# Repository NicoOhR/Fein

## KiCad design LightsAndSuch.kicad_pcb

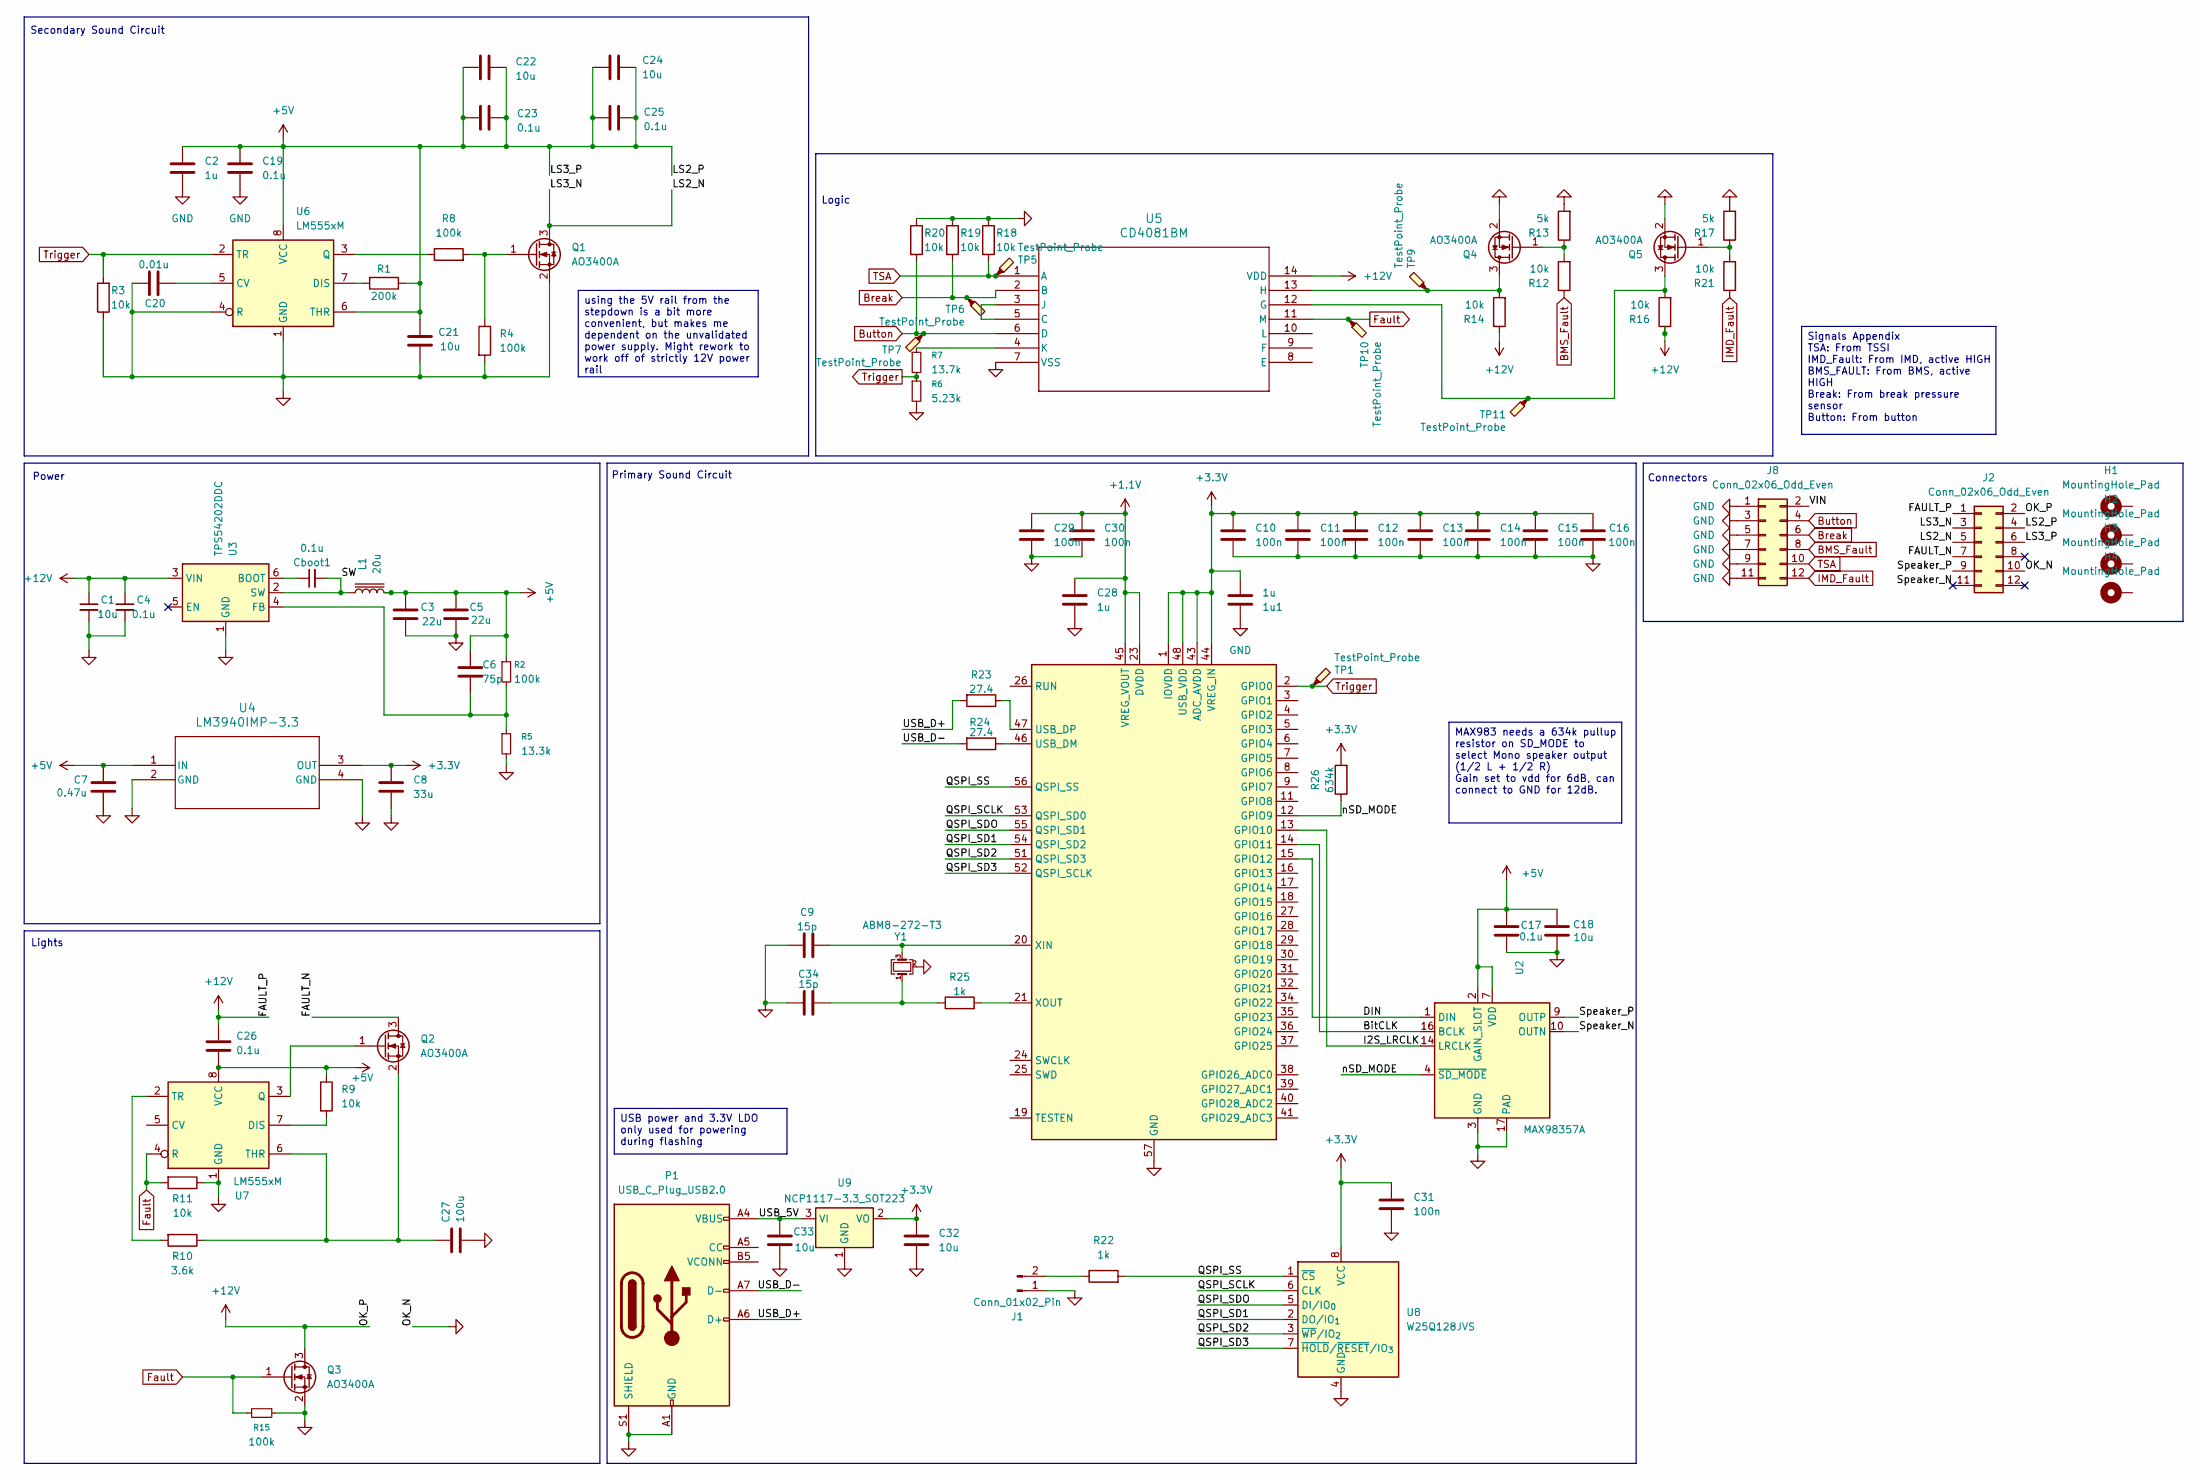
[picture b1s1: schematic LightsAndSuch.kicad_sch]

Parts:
1u1: 1u; C_0603_1608Metric_Pad1.08x0.95mm_HandSolder
C1, C18, C21, C22, C24, C32, C33: 10u; C_0603_1608Metric_Pad1.08x0.95mm_HandSolder
C2, C28: 1u; C_0603_1608Metric_Pad1.08x0.95mm_HandSolder
C3, C5: 22u; C_0603_1608Metric_Pad1.08x0.95mm_HandSolder
C4, C17, C19, C23, C25, C26: 0.1u; C_0603_1608Metric_Pad1.08x0.95mm_HandSolder
C6: 75p; C_0603_1608Metric_Pad1.08x0.95mm_HandSolder
C7: 0.47u; C_0603_1608Metric_Pad1.08x0.95mm_HandSolder
C8: 33u; C_0603_1608Metric_Pad1.08x0.95mm_HandSolder
C9, C34: 15p; C_0603_1608Metric_Pad1.08x0.95mm_HandSolder
C10, C11, C12, C13, C14, C15, C16, C29, C30, C31: 100n; C_0603_1608Metric_Pad1.08x0.95mm_HandSolder
C20: 0.01u; C_0603_1608Metric_Pad1.08x0.95mm_HandSolder
C27: 100u; C_0603_1608Metric_Pad1.08x0.95mm_HandSolder
Cboot1: 0.1u; C_0603_1608Metric_Pad1.08x0.95mm_HandSolder
H1, H2, H3, H4: MountingHole_Pad; MountingHole_4.3mm_M4_DIN965_Pad
J1: Conn_01x02_Pin; PinHeader_1x02_P2.00mm_Vertical
J2, J8: Conn_02x06_Odd_Even; Hirose_DF11-12DP-2DSA_2x06_P2.00mm_Vertical
L1: 20u; L_0603_1608Metric
P1: USB_C_Plug_USB2.0; USB_C_Receptacle_Amphenol_124019772112A
Q1, Q2, Q3, Q4, Q5: AO3400A; SOT-23
R1: 200k; R_0603_1608Metric_Pad0.98x0.95mm_HandSolder
R2, R4, R8, R15: 100k; R_0603_1608Metric_Pad0.98x0.95mm_HandSolder
R3, R9, R11, R12, R14, R16, R18, R19, R20, R21: 10k; R_0603_1608Metric_Pad0.98x0.95mm_HandSolder
R5: 13.3k; R_0603_1608Metric_Pad0.98x0.95mm_HandSolder
R6: 5.23k; R_0603_1608Metric_Pad0.98x0.95mm_HandSolder
R7: 13.7k; R_0603_1608Metric_Pad0.98x0.95mm_HandSolder
R10: 3.6k; R_0603_1608Metric_Pad0.98x0.95mm_HandSolder
R13, R17: 5k; R_0603_1608Metric_Pad0.98x0.95mm_HandSolder
R22, R25: 1k; R_0603_1608Metric_Pad0.98x0.95mm_HandSolder
R23, R24: 27.4; R_0603_1608Metric_Pad0.98x0.95mm_HandSolder
R26: 634k; R_0603_1608Metric_Pad0.98x0.95mm_HandSolder
TP1, TP5, TP6, TP7, TP9, TP10, TP11: TestPoint_Probe; HARWIN_S2761-46R
U1: RP2040; QFN-56-1EP_7x7mm_P0.4mm_EP3.2x3.2mm
U2: MAX98357A; TQFN-16-1EP_3x3mm_P0.5mm_EP1.23x1.23mm
U3: TPS54202DDC; SOT-23-6
U4: LM3940IMP-3.3; MP04A
U5: CD4081BM; DIP-14_W7.62mm
U6, U7: LM555xM; SOIC-8_3.9x4.9mm_P1.27mm
U8: W25Q128JVS; SOIC-8_5.3x5.3mm_P1.27mm
U9: NCP1117-3.3_SOT223; SOT-223-3_TabPin2
Y1: ABM8-272-T3; Crystal_SMD_3225-4Pin_3.2x2.5mm_HandSoldering

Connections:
+1.1V: C28.1, C29.1, C30.1, U1.23 (DVDD), U1.45 (VREG_VOUT), U1.50 (DVDD)
+3.3V: 1u1.2, C8.1, C10.1, C11.1, C12.1, C13.1, C14.1, C15.1, C16.1, C31.1, C32.1, R26.2, U1.1 (IOVDD), U1.10 (IOVDD), U1.22 (IOVDD), U1.33 (IOVDD), U1.42 (IOVDD), U1.43 (ADC_AVDD), U1.44 (VREG_IN), U1.48 (USB_VDD), U1.49 (IOVDD), U4.3 (OUT), U8.8 (VCC), U9.2 (VO)
+5V: C2.1, C3.1, C5.1, C6.1, C7.1, C17.2, C18.2, C19.1, C21.2, C22.1, C22.2, C23.1, C23.2, C24.1, C24.2, C25.1, C25.2, C26.1, J2.4, J2.6, L1.2, R1.1, R2.1, R9.1, U2.2 (GAIN_SLOT), U2.7 (VDD), U2.8 (VDD), U4.1 (IN), U6.6 (THR), U6.8 (VCC), U7.8 (VCC)
+12V: C1.1, C4.1, C26.2, J2.1, J2.2, Q3.3 (D), R14.1, R16.1, U3.3 (VIN), U5.14 (VDD)
/BitCLK: U1.14 (GPIO11), U2.16 (BCLK)
/DIN: U1.15 (GPIO12), U2.1 (DIN)
/FAULT_N: J2.7, Q2.3 (D)
/I2S_LRCLK: U1.13 (GPIO10), U2.14 (LRCLK)
/LS2_N: J2.3, J2.5, Q1.3 (D)
/QSPI_SCLK: U1.53 (QSPI_SD0), U8.6 (CLK)
/QSPI_SD1: U1.54 (QSPI_SD2), U8.2 (DO/IO_{1})
/QSPI_SD2: U1.51 (QSPI_SD3), U8.3 (~WP/IO_{2})
/QSPI_SD3: U1.52 (QSPI_SCLK), U8.7 (~HOLD/~RESET/IO_{3})
/QSPI_SDO: U1.55 (QSPI_SD1), U8.5 (DI/IO_{0})
/QSPI_SS: R22.2, U1.56 (QSPI_SS), U8.1 (~CS)
/SW: Cboot1.2, L1.1, U3.2 (SW)
/Speaker_N: J2.11, U2.10 (OUTN)
/Speaker_P: J2.9, U2.9 (OUTP)
/USB_5V: C33.1, P1.A4 (VBUS), P1.A9 (VBUS), P1.B4 (VBUS), P1.B9 (VBUS), U9.3 (VI)
/USB_D+: P1.A6 (D+), R23.2
/USB_D-: P1.A7 (D-), R24.2
/VIN: J8.2
/nSD_MODE: R26.1, U1.12 (GPIO9), U2.4 (~SD_MODE)
BMS_Fault: J8.8, R12.1
Break: J8.6, R19.2, TP6.1, U5.2 (B)
Button: J8.4, R20.2, TP7.1, U5.6 (D)
Fault: Q3.1 (G), R11.2, R15.2, TP10.1, U5.11 (M), U7.4 (R)
GND: 1u1.1, C1.2, C2.2, C3.2, C4.2, C5.2, C7.2, C8.2, C9.1, C10.2, C11.2, C12.2, C13.2, C14.2, C15.2, C16.2, C17.1, C18.1, C19.2, C20.2, C21.1, C27.1, C28.2, C29.2, C30.2, C31.2, C32.2, C33.2, C34.1, J1.1, J2.10, J8.1, J8.3, J8.5, J8.7, J8.9, J8.11, P1.A1 (GND), P1.A12 (GND), P1.B1 (GND), P1.B12 (GND), P1.S1 (SHIELD), Q1.2 (S), Q3.2 (S), Q4.2 (S), Q5.2 (S), R3.1, R4.2, R5.2, R6.2, R11.1, R13.2, R15.1, R17.2, R18.1, R19.1, R20.1, U1.57 (GND), U2.3 (GND), U2.11 (GND), U2.15 (GND), U2.17 (PAD), U3.1 (GND), U4.2 (GND), U4.4 (GND), U5.7 (VSS), U6.1 (GND), U6.4 (R), U7.1 (GND), U8.4 (GND), U9.1 (GND), Y1.2 (G), Y1.4 (G)
IMD_Fault: J8.12, R21.1
unnamed: C34.2, R25.1, Y1.1
unnamed: J1.2, R22.1
unnamed: Q1.1 (G), R4.1, R8.2
unnamed: Q2.1 (G), U7.3 (Q)
unnamed: C27.2, Q2.2 (S), R10.1, U7.6 (THR)
unnamed: Q4.3 (D), R14.2, TP9.1, U5.13 (H)
unnamed: Q4.1 (G), R12.2, R13.1
unnamed: Q5.3 (D), R16.2, TP11.1, U5.12 (G)
unnamed: Q5.1 (G), R17.1, R21.2
unnamed: R24.1, U1.46 (USB_DM)
unnamed: R23.1, U1.47 (USB_DP)
unnamed: C9.2, U1.20 (XIN), Y1.3
unnamed: R25.2, U1.21 (XOUT)
unnamed: Cboot1.1, U3.6 (BOOT)
unnamed: C6.2, R2.2, R5.1, U3.4 (FB)
unnamed: U5.3 (J), U5.5 (C)
unnamed: R7.1, U5.4 (K)
unnamed: C20.1, U6.5 (CV)
unnamed: R1.2, U6.7 (DIS)
unnamed: R8.1, U6.3 (Q)
unnamed: R9.2, U7.7 (DIS)
unnamed: R10.2, U7.2 (TR)
TSA: J8.10, R18.2, TP5.1, U5.1 (A)
Trigger: R3.2, R6.1, R7.2, TP1.1 (1_1), U1.2 (GPIO0), U6.2 (TR)

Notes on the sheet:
Logic
Lights
Secondary Sound Circuit
Connectors
Power
Primary Sound Circuit
Signals Appendix TSA: From TSSI IMD_Fault: From IMD, active HIGH BMS_FAULT: From BMS, active HIGH Break: From break pressure sensor Button: From button
USB power and 3.3V LDO only used for powering during flashing
using the 5V rail from the stepdown is a bit more convenient, but makes me dependent on the unvalidated power supply. Might rework to work off of strictly 12V power rail
MAX983 needs a 634k pullup resistor on SD_MODE to select Mono speaker output (1/2 L + 1/2 R) Gain set to vdd for 6dB, can connect to GND for 12dB.

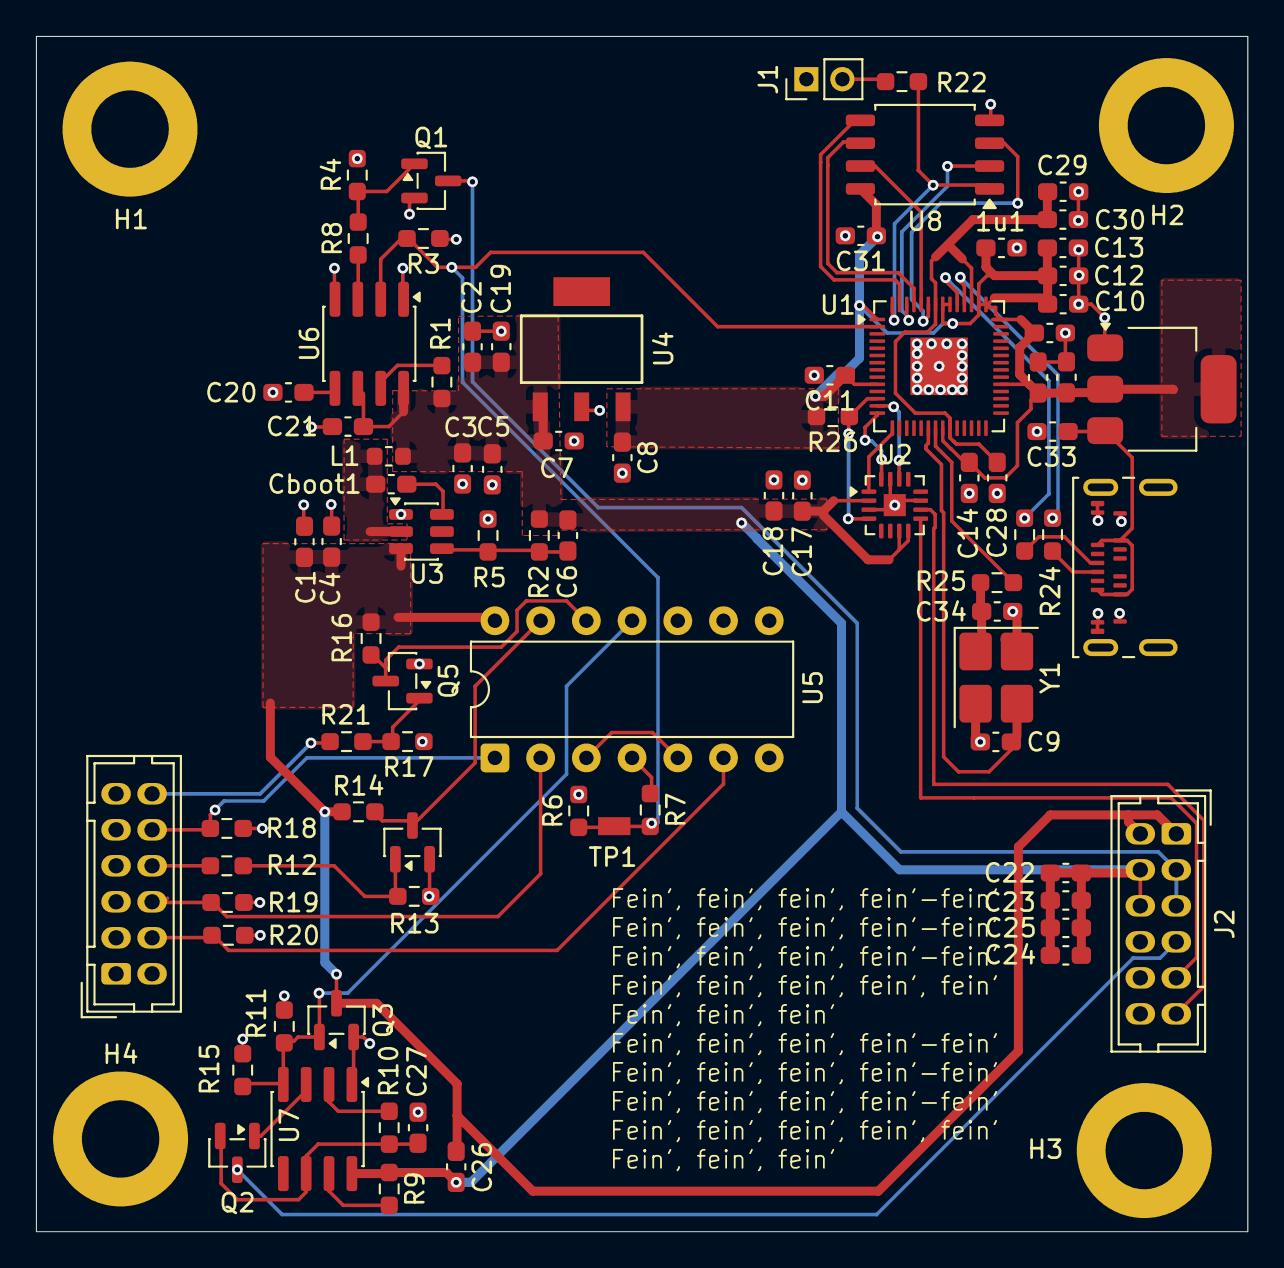
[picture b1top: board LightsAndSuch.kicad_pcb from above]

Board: 4 copper layers, 67.3 x 66.4 mm, 87 parts (0 on the bottom side), 52 nets.

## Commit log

2025-08-09 init commit, components and power set up
2025-08-09 decoupling capacitors for uC and DAC
2025-08-10 uC to amp connections
2025-08-10 changed AND gate, all connections should be finished
2025-08-10 amend to last commit
2025-08-12 incomplete calcs for TPS
2025-08-15 finished math
2025-08-19 added secondary circuit
2025-08-24 finished lights
2025-08-24 flattened file into one sheet
2025-09-03 added missing capacitor for the 555
2025-09-25 most values set in and pull up resistors
2025-09-26 added mosfets to account for 555 current output, sized low side driver for green light
2025-09-26 SWD connector
2025-11-03 footprints selected and grouped
2025-11-07 ground plane and cutouts
2025-11-10 more or less finished with power
2025-11-14 finished power layout + inverted sig
2025-11-15 I/O stuff
2025-11-19 4 layer + buzzer circuit
2025-11-25 rp2040
2025-12-26 rev 1
2026-01-05 grounding out and moving some
2026-01-05 slightly smaller board and thicker power lines
2026-01-06 switching out the connectors need to fix net names
2026-01-06 changed from global labels to net labels
2026-02-15 some updates
2026-02-27 some decoup caps
2026-03-15 passing DRC
2026-03-16 need to route test points
2026-04-14 init
2026-04-15 changes from aiden's computer
2026-04-15 ignoring lock files
